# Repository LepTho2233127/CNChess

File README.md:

# CNChess - Automated Chess System
Automated chess board for playing against chess engine. For more information concerning the hardware needed visit the [wiki](https://github.com/LepTho2233127/CNChess/wiki)

<div align="center">

</div>

## Get Started for Software Development

### 1. Clone project
    git clone <REPO_URL>

### 2. Install Ubuntu WSL (only if on windows)

[Instructions](https://learn.microsoft.com/en-us/windows/wsl/install)

### 3. Open WSL inside project folder

### 4. Install docker

```bash
sudo apt update && sudo apt upgrade
```

[Instructions](https://docs.docker.com/engine/install/ubuntu/)

### 5. If on WSL, give access to USB port to WSL 

```bash
winget install --interactive --exact dorssel.usbipd-win
```

> [!IMPORTANT]
> Run the following commands as admin in PowerShell. You also need to keep a WSL active

```PowerShell
usbipd list
usbipd bind --busid 4-4
usbipd attach --wsl --busid <busid>
```

In WSL, check if you see the device you just attached
```bash
lsusb
```

### 6. Build docker image
```bash
sudo docker compose build
```

### 7. Give docker access to window 
```bash
xhost +local:docker
```

### 8. Run code
```bash
sudo docker compose run cnchess
```

### 9. Close docker (or ctrl-c)
```bash
sudo docker compose down
```
> [!NOTE]
> If you are on a Linux operating systems, it is possible to not use Docker by following this procedure

### 1. Install Stockfish at default location
```bash
sudo apt update
sudo apt install stockfish
which stockfish
```
>[!IMPORTANT]
>If path obtained when running which command is not /usr/games/stockfish, you need to change it in CNChess.py file manually

### 2. Install Python libraries
Inside CNChess directory run : 

```bash
cd python
python -m venv .venv
source .venv/bin/activate
pip install -r requirements.txt
```

### 3. Run the project
With right hardware, run this command in python directory with virtual environment activated
```bash
python main.py
```
If no camera or serial port is detected, you might need to change it respectively inside Cam.py or Communication.py.

## Documentation
Additional software documentation is available and generated using MkDocs [docs](https://leptho2233127.github.io/CNChess/). Run `mkdocs build` inside project directory to build it.
Located inside docs_build directory, open in a browser to access it.

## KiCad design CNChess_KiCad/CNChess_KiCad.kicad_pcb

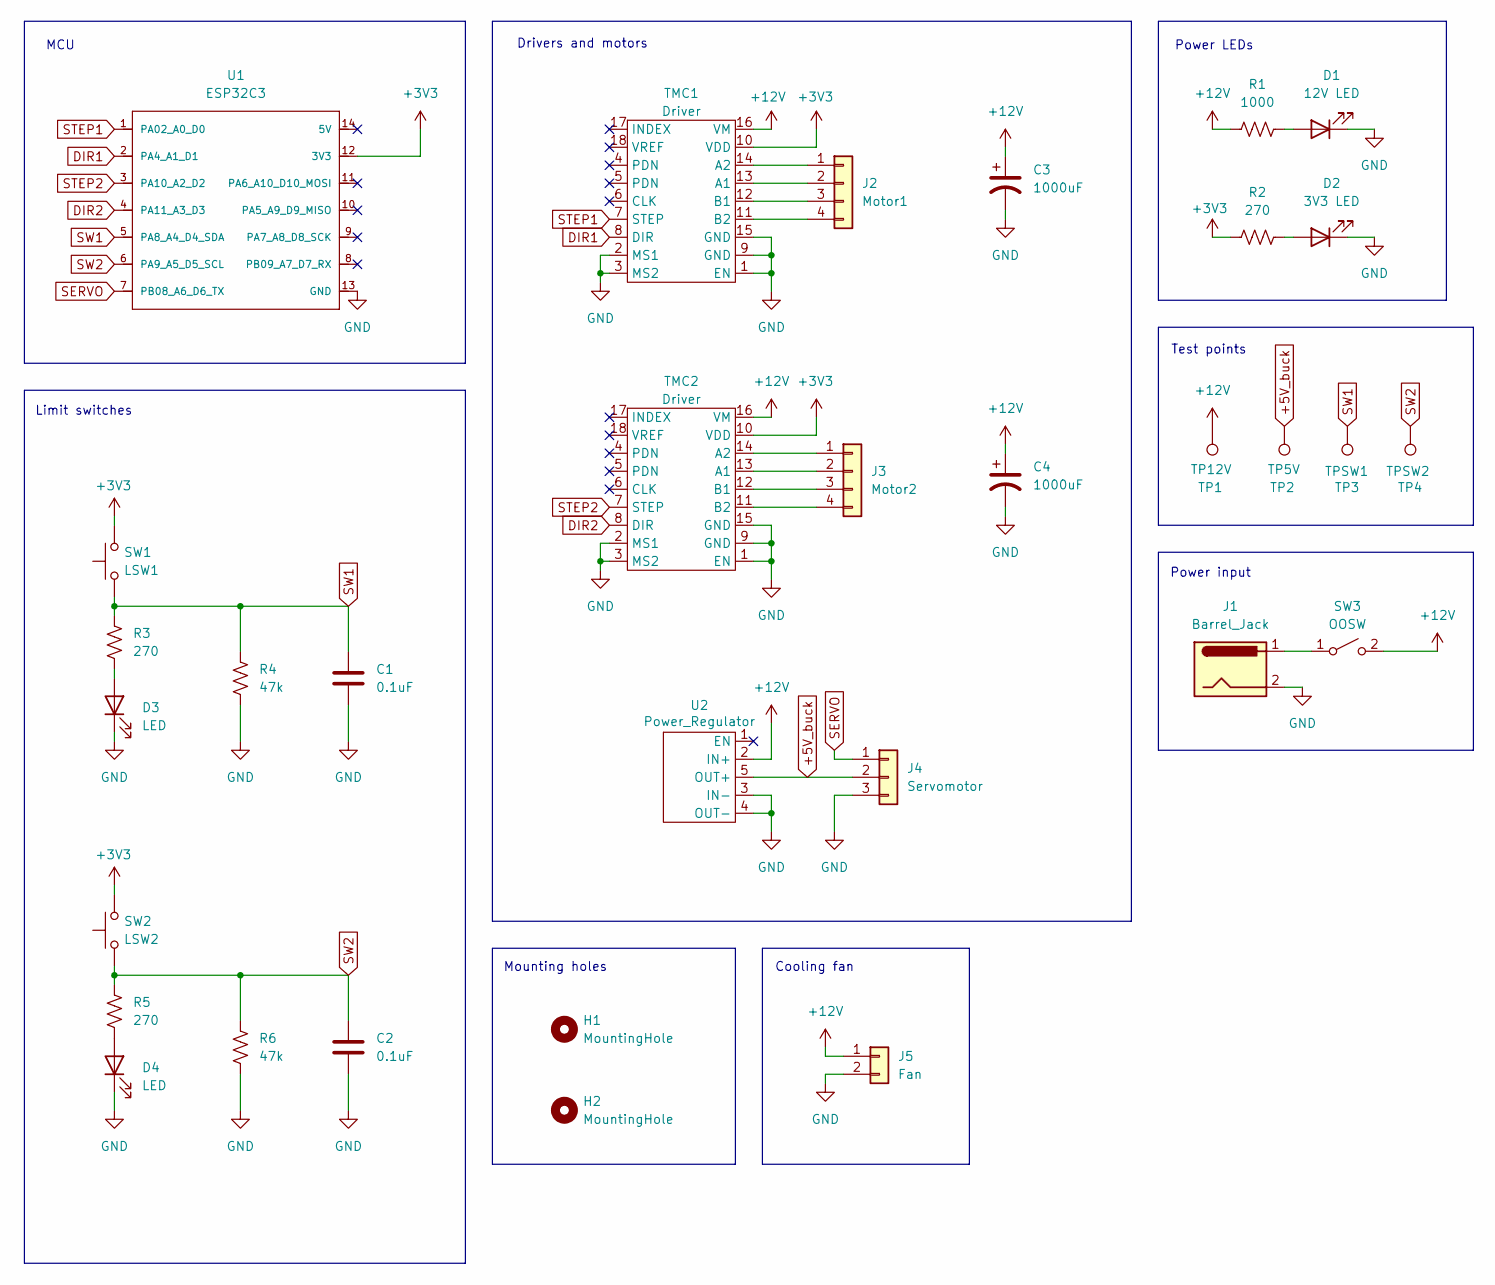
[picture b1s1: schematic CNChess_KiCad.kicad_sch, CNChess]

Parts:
C1, C2: 0.1uF; CAP0_1u
C3, C4: 1000uF; CP_Radial_D10.0mm_P5.00mm
D1: 12V LED; JST_XH_B2B-XH-A_1x02_P2.50mm_Vertical
D2: 3V3 LED; JST_XH_B2B-XH-A_1x02_P2.50mm_Vertical
D3, D4: LED; JST_XH_B2B-XH-A_1x02_P2.50mm_Vertical
H1, H2: MountingHole; MountingHole_3.2mm_M3_Pad
J1: Barrel_Jack; BarrelJack_Horizontal
J2: Motor1; JST_XH_B4B-XH-A_1x04_P2.50mm_Vertical
J3: Motor2; JST_XH_B4B-XH-A_1x04_P2.50mm_Vertical
J4: Servomotor; JST_XH_B3B-XH-A_1x03_P2.50mm_Vertical
J5: Fan; JST_XH_B2B-XH-A_1x02_P2.50mm_Vertical
R1: 1000; R_Axial_DIN0204_L3.6mm_D1.6mm_P5.08mm_Horizontal
R2, R3, R5: 270; R_Axial_DIN0204_L3.6mm_D1.6mm_P5.08mm_Horizontal
R4, R6: 47k; R_Axial_DIN0204_L3.6mm_D1.6mm_P5.08mm_Horizontal
SW1: LSW1; JST_XH_B2B-XH-A_1x02_P2.50mm_Vertical
SW2: LSW2; JST_XH_B2B-XH-A_1x02_P2.50mm_Vertical
SW3: OOSW; JST_XH_B2B-XH-A_1x02_P2.50mm_Vertical
TMC1, TMC2: Driver; TMC2209
TP1: TP12V; TestPoint_Pad_D1.5mm
TP2: TP5V; TestPoint_Pad_D1.5mm
TP3: TPSW1; TestPoint_Pad_D1.5mm
TP4: TPSW2; TestPoint_Pad_D1.5mm
U1: ESP32C3; Esp32-C3
U2: Power_Regulator; Reg_12V

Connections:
+3V3: R2.1, SW1.2, SW2.2, TMC1.10 (VDD), TMC2.10 (VDD), U1.12 (3V3)
+5V_buck: J4.2, TP2.1, U2.5 (OUT+)
+12V: C3.1, C4.1, J5.1, R1.1, SW3.2 (B), TMC1.16 (VM), TMC2.16 (VM), TP1.1, U2.2 (IN+)
DIR1: TMC1.8 (DIR), U1.2 (PA4_A1_D1)
DIR2: TMC2.8 (DIR), U1.4 (PA11_A3_D3)
GND: C1.2, C2.2, C3.2, C4.2, D1.1 (K), D2.1 (K), D3.1 (K), D4.1 (K), J1.2, J4.3, J5.2, R4.1, R6.1, TMC1.1 (EN), TMC1.2 (MS1), TMC1.3 (MS2), TMC1.9 (GND), TMC1.15 (GND), TMC2.1 (EN), TMC2.2 (MS1), TMC2.3 (MS2), TMC2.9 (GND), TMC2.15 (GND), U1.13 (GND), U2.3 (IN-), U2.4 (OUT-)
unnamed: D1.2 (A), R1.2
unnamed: D2.2 (A), R2.2
unnamed: D3.2 (A), R3.1
unnamed: D4.2 (A), R5.1
unnamed: J2.1, TMC1.14 (A2)
unnamed: J2.2, TMC1.13 (A1)
unnamed: J2.3, TMC1.12 (B1)
unnamed: J2.4, TMC1.11 (B2)
unnamed: J3.1, TMC2.14 (A2)
unnamed: J3.2, TMC2.13 (A1)
unnamed: J3.3, TMC2.12 (B1)
unnamed: J3.4, TMC2.11 (B2)
unnamed: J1.1, SW3.1 (A)
SERVO: J4.1, U1.7 (PB08_A6_D6_TX)
STEP1: TMC1.7 (STEP), U1.1 (PA02_A0_D0)
STEP2: TMC2.7 (STEP), U1.3 (PA10_A2_D2)
SW1: C1.1, R3.2, R4.2, SW1.1, TP3.1, U1.5 (PA8_A4_D4_SDA)
SW2: C2.1, R5.2, R6.2, SW2.1, TP4.1, U1.6 (PA9_A5_D5_SCL)

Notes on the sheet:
Limit switches
Mounting holes
Drivers and motors
Cooling fan
Test points
MCU
Power LEDs
Power input

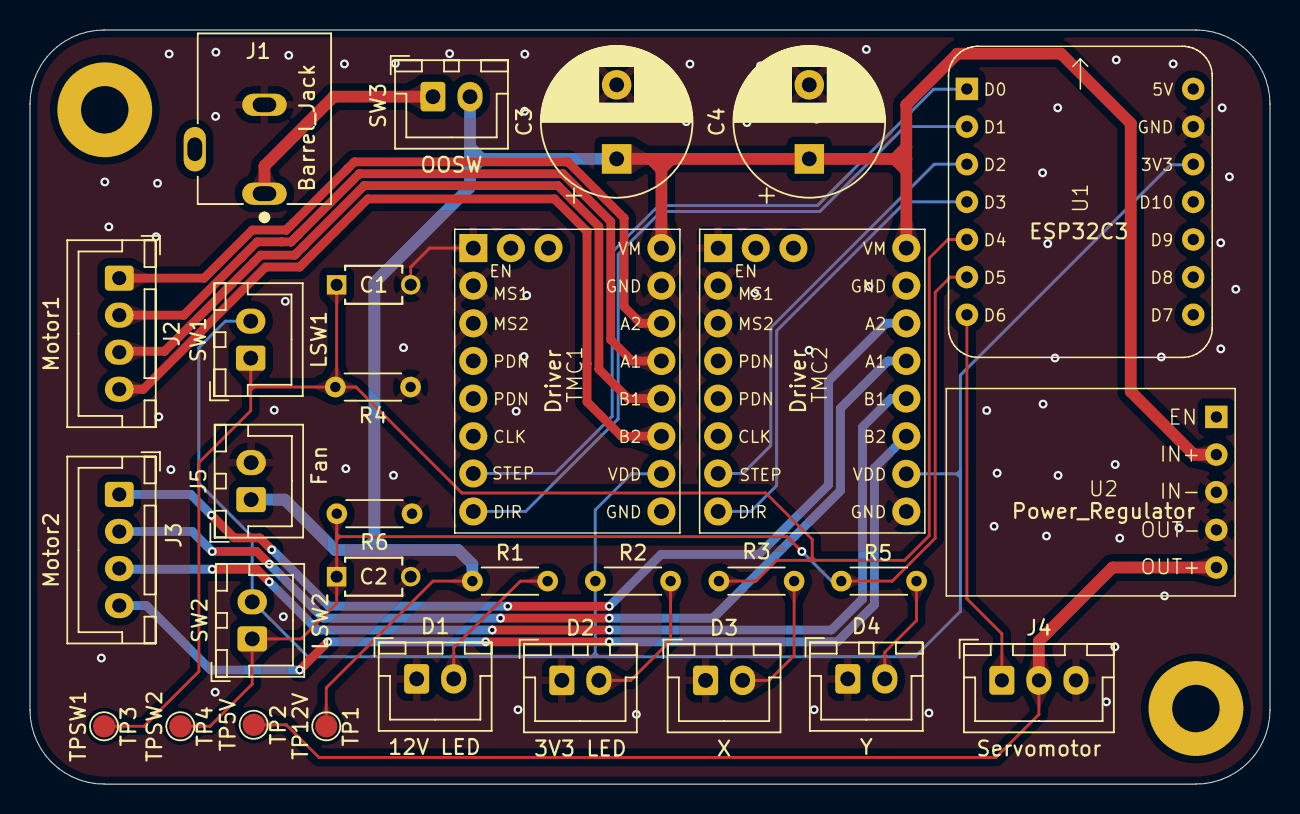
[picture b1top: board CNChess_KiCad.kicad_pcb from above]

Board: 2 copper layers, 83.7 x 50.9 mm, 32 parts (0 on the bottom side), 24 nets.

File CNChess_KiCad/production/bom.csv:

Designator,Footprint,Quantity,Value,LCSC Part #
"C1, C2",CAP0_1u,2,0.1uF,
"C3, C4",CP_Radial_D10.0mm_P5.00mm,2,1000uF,
D1,JST_XH_B2B-XH-A_1x02_P2.50mm_Vertical,1,12V LED,
D2,JST_XH_B2B-XH-A_1x02_P2.50mm_Vertical,1,3V3 LED,
D3,JST_XH_B2B-XH-A_1x02_P2.50mm_Vertical,1,X,
D4,JST_XH_B2B-XH-A_1x02_P2.50mm_Vertical,1,Y,
J1,BarrelJack_Horizontal,1,Barrel_Jack,
J2,JST_XH_B4B-XH-A_1x04_P2.50mm_Vertical,1,Motor1,
J3,JST_XH_B4B-XH-A_1x04_P2.50mm_Vertical,1,Motor2,
J4,JST_XH_B3B-XH-A_1x03_P2.50mm_Vertical,1,Servomotor,
J5,JST_XH_B2B-XH-A_1x02_P2.50mm_Vertical,1,Fan,
R1,R_Axial_DIN0204_L3.6mm_D1.6mm_P5.08mm_Horizontal,1,1000,
"R2, R3, R5",R_Axial_DIN0204_L3.6mm_D1.6mm_P5.08mm_Horizontal,3,270,
"R4, R6",R_Axial_DIN0204_L3.6mm_D1.6mm_P5.08mm_Horizontal,2,47k,
SW1,JST_XH_B2B-XH-A_1x02_P2.50mm_Vertical,1,LSW1,
SW2,JST_XH_B2B-XH-A_1x02_P2.50mm_Vertical,1,LSW2,
SW3,JST_XH_B2B-XH-A_1x02_P2.50mm_Vertical,1,OOSW,
"TMC1, TMC2",TMC2209,2,Driver,
TP1,TestPoint_Pad_D1.5mm,1,TP12V,
TP2,TestPoint_Pad_D1.5mm,1,TP5V,
TP3,TestPoint_Pad_D1.5mm,1,TPSW1,
TP4,TestPoint_Pad_D1.5mm,1,TPSW2,
U1,Esp32-C3,1,ESP32C3,
U2,Reg_12V,1,Power_Regulator,

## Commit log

2026-01-13 remise proposition de projet
2026-01-13 addition de library
2026-01-13 Mise à jour du README.md pour ajouter des instructions détaillées sur l'utilisation de PowerShell et le workflow Git recommandé
2026-01-14 update read me
2026-01-14 add platform io program and made basic structure
2026-01-14 Fix formatting in README.md for installation verification section
2026-01-14 readme update
2026-01-14 fix readme command for linux
2026-01-14 modifiy read me ahgain
2026-01-14 added basic python file
2026-01-14 add basic file
2026-01-14 basic chess
2026-01-14 fix typo
2026-01-14 change depth
2026-01-14 start of docker file, stockfish not working
2026-01-14 working docker
2026-01-14 update docker compose and read me
2026-01-14 add control file
2026-01-14 fix link
2026-01-14 fix number
2026-01-14 kicad project and schematic added to repository
2026-01-15 basic path finding for computer move
2026-01-15 remove print
2026-01-15 moved comment
2026-01-15 removed useless device
2026-01-15 start of ui remade the board -start of movement -docker file
2026-01-19 changed ui to pyqt6 using mvc structure, docker not yet working
2026-01-21 Add trajectory calculation and update control logic for piece movement
2026-01-21 removed Empty directory
2026-01-21 add accelstepper library
2026-01-21 refactor a little bit and added make move function
2026-01-21 addition of primitive send_cmd
2026-01-26 now possible to play next step is to make it work with docker
2026-01-26 update kicad schematic
2026-01-27 remise tableau de bord 1
2026-01-27 First implementation of stepper control on esp32
2026-01-27 refactor command handling by removing CommandType enum and simplifying switch cases
2026-01-27 PCB tracks + remise tableau de bord 1
2026-01-27 updated docker file to run ui
2026-01-28 update readme to add xhost command
2026-01-28 fix small typo
2026-01-28 clean up of ui
2026-01-28 working path finding preview
2026-01-28 removing piece is now working but it doesnt deactivate magnet between 2 path
2026-01-28 made code build
2026-01-28 add new command class with magnet state
2026-01-28 ajout des modèles 3d et terminé V1 du PCB
2026-01-28 ajout_class_command
2026-01-28 ajustement modeles 3d
2026-01-28 add port in docker
2026-01-28 wip chess_controler
2026-01-28 start of refactor for esp32, not working right now and communication still to do
2026-01-30 Trop cool peut faire carré
2026-01-30 square loop and update gitignore
2026-01-30 start of homing and communication pretty much working
2026-02-02 Addition of servo control and working homing procedure
2026-02-02 addition of a condition for faster homing movement
2026-02-03 changed distance value for homing
2026-02-03 start of core xy control
2026-02-03 still work to do to adapt to our needs, now in embedded its not possible to move from x and y position
2026-02-03 pass control as argument to chess controller class
2026-02-03 separate communication
2026-02-03 small fix
2026-02-03 fix import
2026-02-03 added move and chessmove communication
2026-02-03 position working
2026-02-03 update remove piece posiiton
2026-02-03 ready to test control ui
2026-02-03 addition of jog
2026-02-03 adjusted get step
2026-02-03 optimized path
2026-02-03 FAST HOME EVERYTIME
2026-02-03 servo to move piece working
2026-02-03 update elec et TBsem5
2026-02-03 Mask bleu et jaune camera
2026-02-03 fix edge case
2026-02-03 make communication faster
2026-02-03 mapping de la grid
2026-02-03 pcb ready
2026-02-03 fix diagonal path finding
2026-02-11 castle working
2026-02-11 refactor logic in chess controller (more modular)
2026-02-11 add en passant
2026-02-11 reactivate computer
2026-02-11 refactor assets directory, update readme. UI working
2026-02-11 add drop peice sequence
2026-02-11 Test avec image importé. met point au milieu des cases
2026-02-11 start of new ui
2026-02-11 settings view created
2026-02-11 update home page
2026-02-11 can detect piece
2026-02-11 dimension of board
2026-02-15 small change in new ui
2026-02-15 added logic for home page in python
2026-02-16 small changes to ui
2026-02-16 added main window add start of logic to move between pages
2026-02-17 remove remise
2026-02-18 add grid for board
2026-02-18 grid working with resizing
2026-02-18 settings grid implemented
2026-02-18 working on real prototype
2026-02-18 settings page before controller
2026-02-18 pieces images almost working
2026-02-18 give UCI for move with two different board position
2026-02-18 reste a coder controller da la settings page
2026-02-19 light cleanup
2026-02-19 added signal for clicking square
2026-02-20 game working again, highlight of move added
2026-02-20 fixed small icon problem and logic issue in the main ui
2026-02-23 added start of list history
2026-02-24 resign button
2026-02-24 start button fixed
2026-02-25 change servo top position
2026-02-25 remove new control from view
2026-02-25 add make move to game controller
2026-02-25 add repaint
2026-02-25 remove old ui
2026-02-25 add waiting dialog
2026-02-25 fixed movement with pcb
2026-02-25 add impossible difficuly
2026-02-25 Refactor code structure for improved readability and maintainability
2026-02-25 changed esay difficulty and drop piece
2026-03-02 refactor for flipping black square
2026-03-05 playing with black now working
2026-03-07 fixed easy difficulty
2026-03-07 create dialog file and checkmate dialog
2026-03-07 added checkmate dialog to game page
2026-03-07 checkmate dialog working
2026-03-08 timer are now working
2026-03-08 added turn indicator
2026-03-09 fix white or black clock
2026-03-09 fix reset black clock
2026-03-09 added draw dialog and fix bug with play again button in dialogs
2026-03-09 added spinning gear to waiting dialog
2026-03-11 add path
2026-03-11 beginner difficulty selected by default
2026-03-11 fix trajectory
2026-03-11 fix small issue when not selecting legal moves
2026-03-11 fix diagonal bug
2026-03-11 checkmate eat king
2026-03-11 time toggle improvement
2026-03-11 nothing
2026-03-11 fix crash
2026-03-11 fixed thread bug but waiting screen black when checkmate
2026-03-11 wip_cam
2026-03-11 addition of dependencies
2026-03-11 remove basic pacakge
2026-03-11 promotion working
2026-03-11 basic move detection working on real board
2026-03-11 out of time dialog
2026-03-11 fix calibration
2026-03-11 recalibrate servo motor and added button pin
2026-03-15 added evaluation function and start time button
2026-03-15 added score and changed how start time works
2026-03-15 start of move back button
2026-03-18 made square darker
2026-03-18 final files
2026-03-18 refactor a bit settings page
2026-03-18 remove unused file
2026-03-18 rename go_home and added com to main and settings page
2026-03-18 add cam scan to ui
2026-03-18 addition of playbutton management
2026-03-18 com settings v1
2026-03-18 add on cam click function
2026-03-18 com settings v2
2026-03-18 added condition and setting page signal
2026-03-18 commit v2
2026-03-18 added signal
2026-03-18 addition of castling detection
2026-03-18 cam working on htis commit
2026-03-18 working
2026-03-18 increase timeout delay
2026-03-18 fixed qobject controller
2026-03-18 fixed castling detection
2026-03-18 servo command added to access from settings
2026-03-18 addition of possibility to retake picture
2026-03-18 decomenter ligne celeste
2026-03-18 prend info du board au lieu de la caméra avant move du joueur
2026-03-18 Add custom message handling for button press waiting state
2026-03-18 added camera to settings page
2026-03-20 now possible to control gantry with ui
2026-03-20 recalibration of servo and z working in ui
2026-03-23 grid added to settings page
2026-03-23 QSS essais
2026-03-25 made square_size global variable and added real 0 0
2026-03-25 fix my problem
2026-03-25 cest laid
2026-03-25 added offset and fixed blocking ui
2026-03-25 fixed offset for real
2026-03-25 qss theme added
2026-03-25 invert row in cam to fit board
2026-03-25 changed turn indicator
2026-03-25 new calib
2026-03-25 fixed size of geat
2026-03-25 fixed turn indicator problem and added thread clean up
2026-03-25 added thread for home com
2026-03-25 fixed gear label
2026-03-25 try to fix thread program
2026-03-25 addition of 3 frame validation before sending move
2026-03-25 decrease to 0.1 sec between frame
2026-03-25 home page done
2026-03-25 fixed problem with clock and slowed delay of cam
2026-03-25 home page done v2
2026-03-25 better logo
2026-03-25 new process image is old preocess frame. no more old process image
2026-03-26 fix hanging thread (claude mvp)
2026-03-26 add move revert
2026-03-27 made back button in settings page return to right page
2026-03-27 fixed going back button
2026-03-27 fixed problem with time when invalid move, made calibration possible with ui and added invalid move dialog
2026-03-29 made image the size of button for difficulty
2026-03-29 added outline to game page
2026-03-29 added piece image for promotion
2026-04-01 changed diffivulty icon
2026-04-01 start of addinf docstring
2026-04-01 refactor cam
2026-04-01 camp.py comment in doc strings
2026-04-01 added more comments to game page
2026-04-01 refactor promotion widget and finished comment in game_page.py
2026-04-01 remove unused assets
2026-04-01 remove .vscode folder
2026-04-01 remove imwrite
2026-04-01 new points
2026-04-01 fixed homing in settings page
2026-04-01 image is updating in setting page and fixed streching issue with move history
2026-04-01 same
2026-04-01 fixed full screen issue
2026-04-01 initial image
2026-04-01 made home page look better in full screen
2026-04-01 added escape button to quit application and F11 to full screen
2026-04-08 made waiting text bigger and changed color icon
2026-04-08 new image that fits the other
2026-04-09 added promotion detection in camera and made message text bigger
2026-04-09 finish comments and clean up
2026-04-09 python code documentation and small fix in move list
2026-04-09 updated code documentation
2026-04-10 updated documentation layout
2026-04-10 added time control and fix bug when not plugged into esp32
2026-04-10 added mcdoc docs
2026-04-10 changed folder for documentation
2026-04-10 Revise README with project details and setup instructions
    Updated project title and added a brief description and getting started instructions.
2026-04-10 Enhance README with installation and usage details
    Updated formatting and added hardware information to the README.
2026-04-10 Update clone command URL placeholder in README
2026-04-13 Fix README instruction for stockfish path update
2026-04-13 added comments and clean up main.cpp
2026-04-15 small fix in code and changed docs directory for github pages
2026-04-15 final documentation
2026-04-15 Update MkDocs documentation link in README
    Updated documentation link for MkDocs.
2026-04-15 final update to project, fix camera image in settings page update
2026-04-15 Parts to manufacture
2026-04-15 All the parts of the board and chess pieces
2026-04-16 fixed weird nose and fix homing while waiting for button press
2026-04-18 Add image to README for visual reference
    Added an image to the README for better visualization.
2026-04-18 remove useless directory
2026-05-03 Update README with new image and setup instructions
    Added an additional image and a section for getting started with software development.
2026-05-03 Add center-aligned image to README
2026-05-03 Fix README formatting by adding closing div tag
    Added closing div tag for alignment in README.
